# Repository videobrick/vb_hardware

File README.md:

hardware
========

OSHW Video Interface Hardware

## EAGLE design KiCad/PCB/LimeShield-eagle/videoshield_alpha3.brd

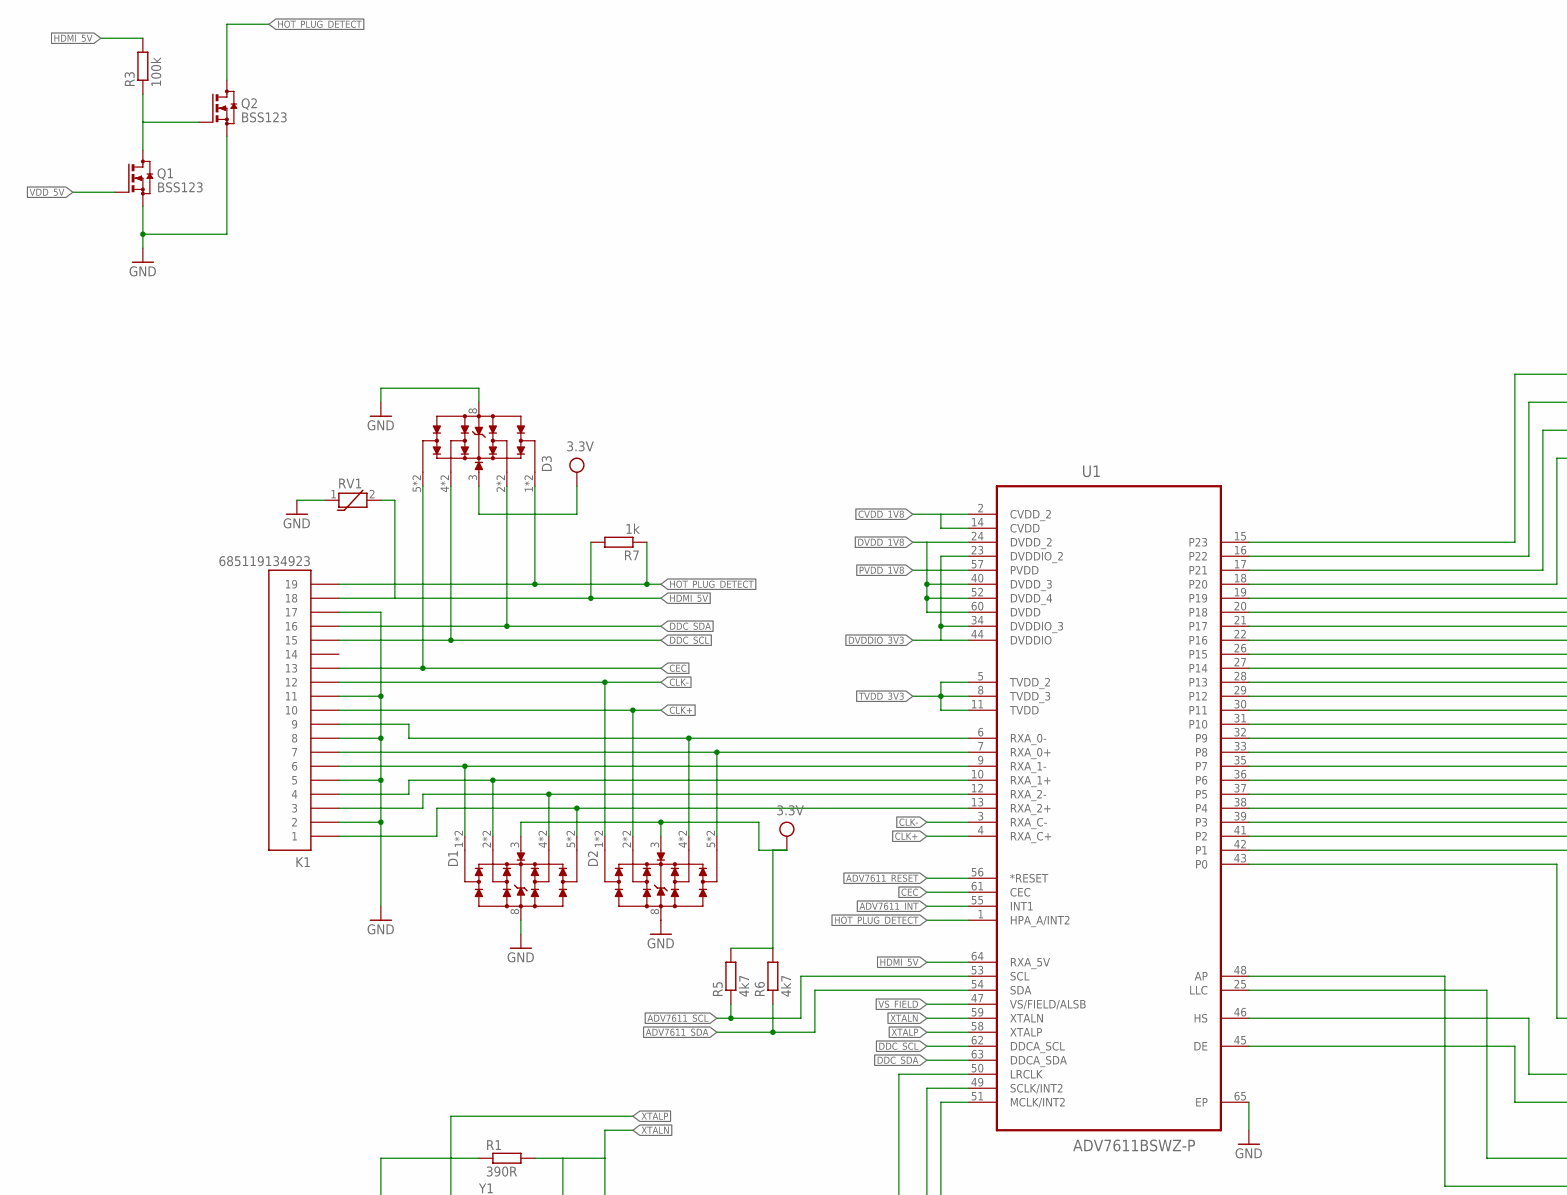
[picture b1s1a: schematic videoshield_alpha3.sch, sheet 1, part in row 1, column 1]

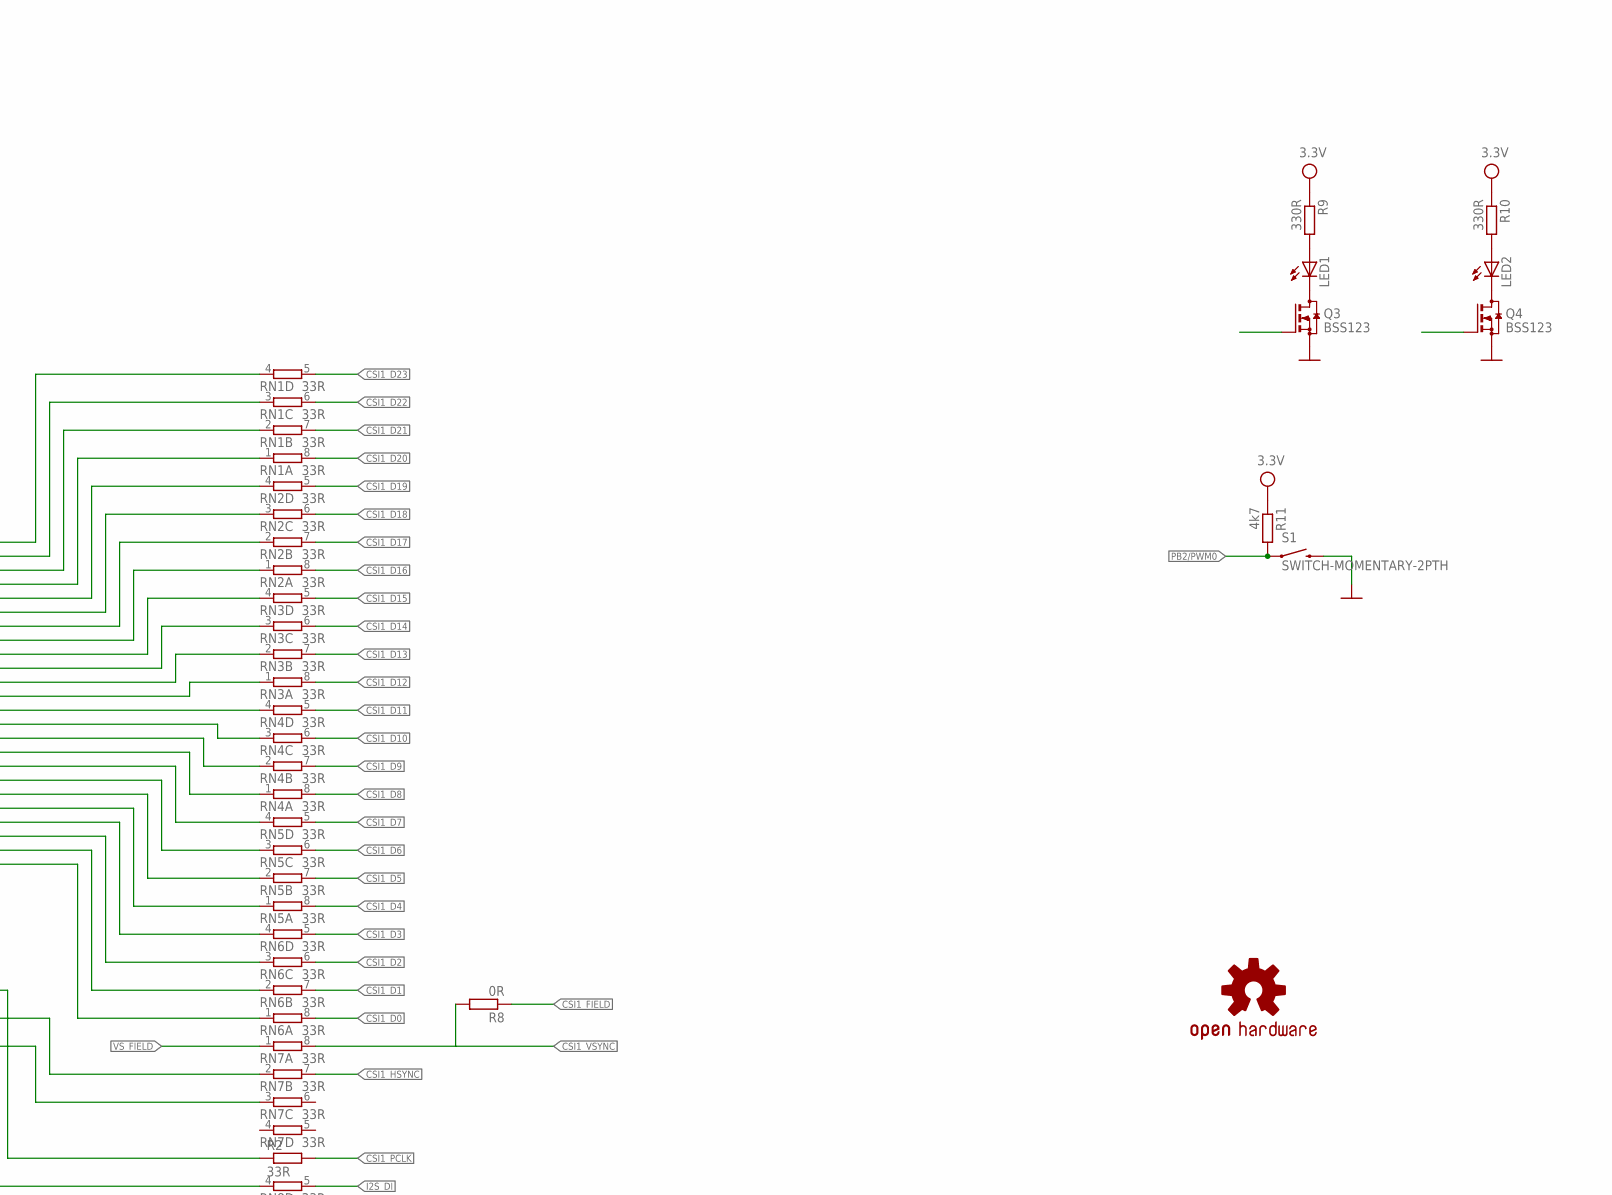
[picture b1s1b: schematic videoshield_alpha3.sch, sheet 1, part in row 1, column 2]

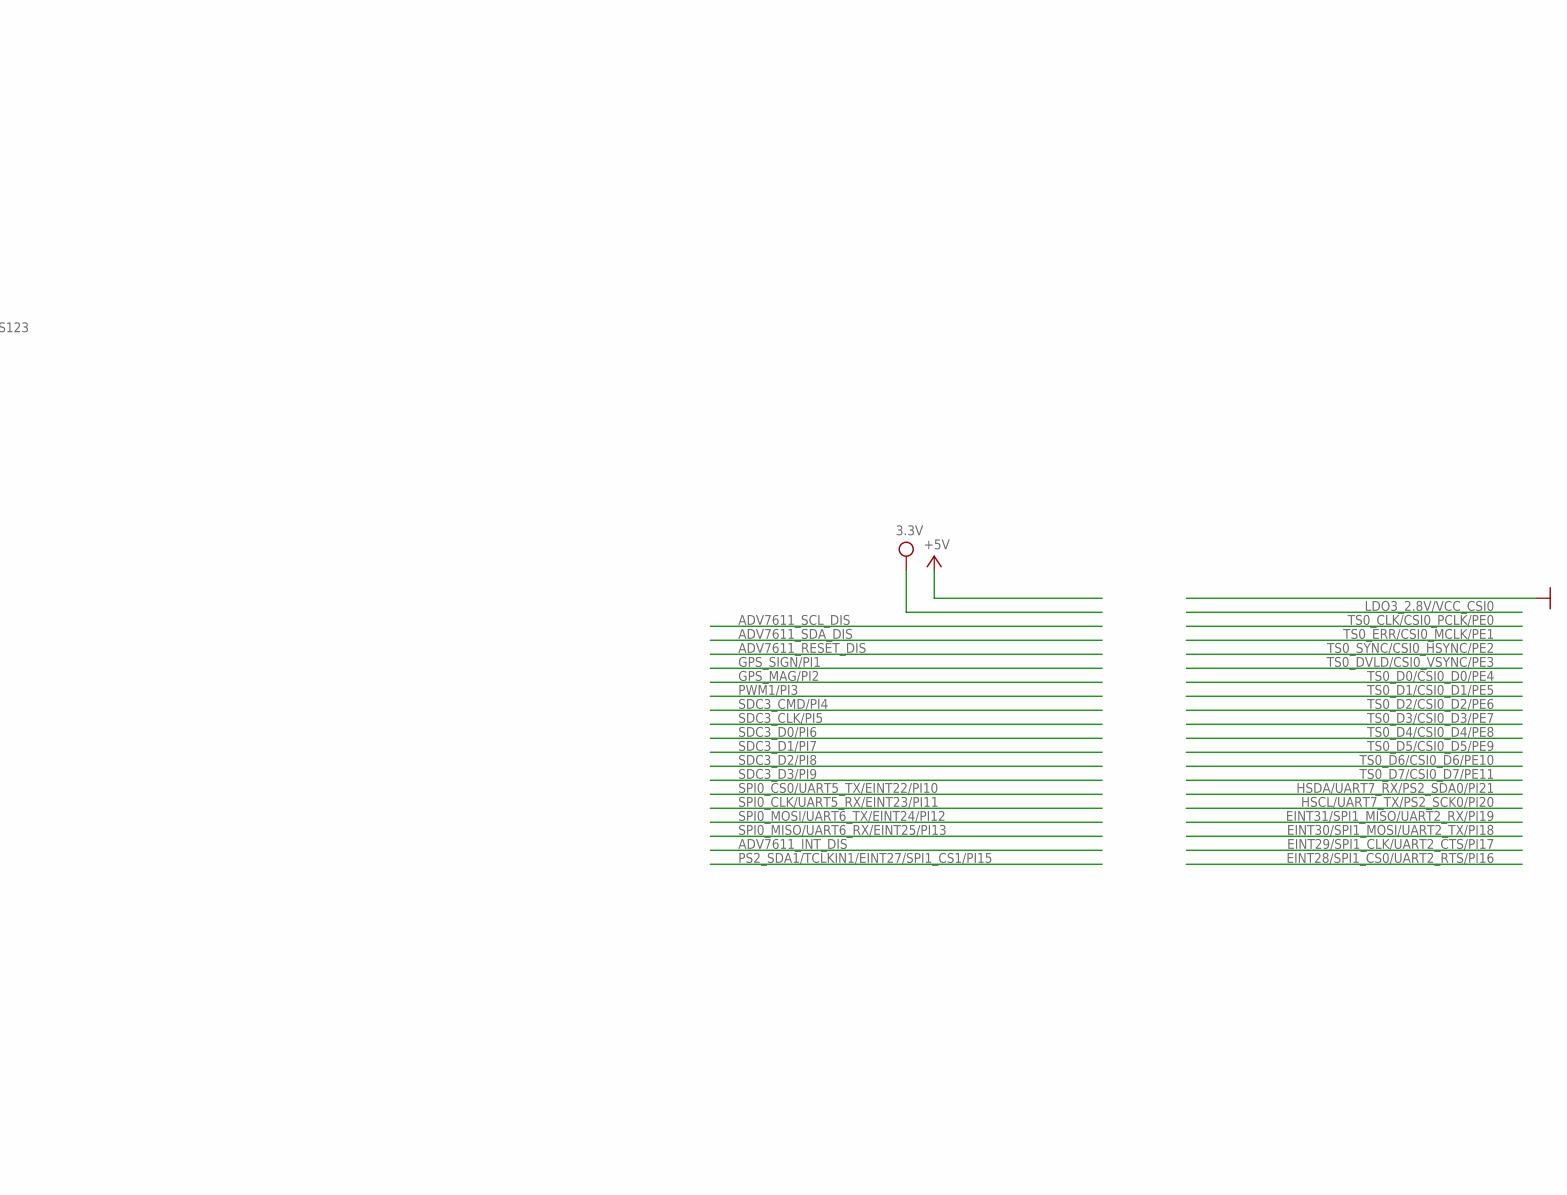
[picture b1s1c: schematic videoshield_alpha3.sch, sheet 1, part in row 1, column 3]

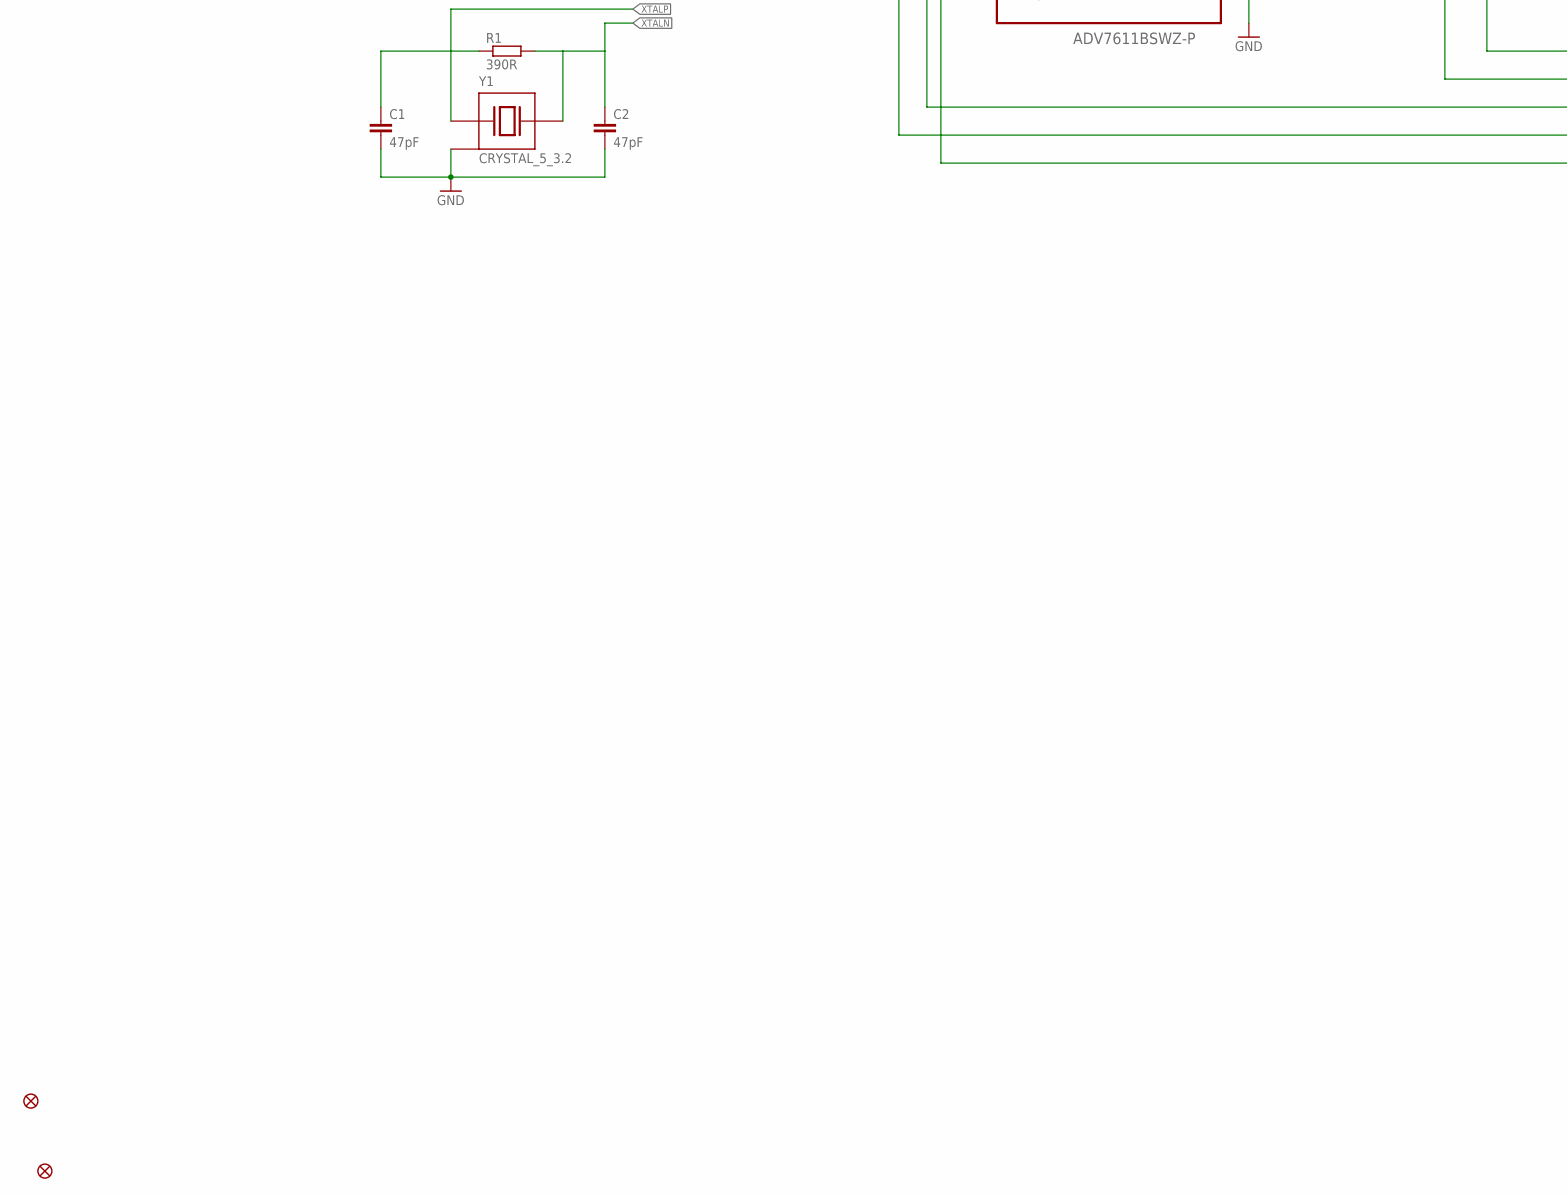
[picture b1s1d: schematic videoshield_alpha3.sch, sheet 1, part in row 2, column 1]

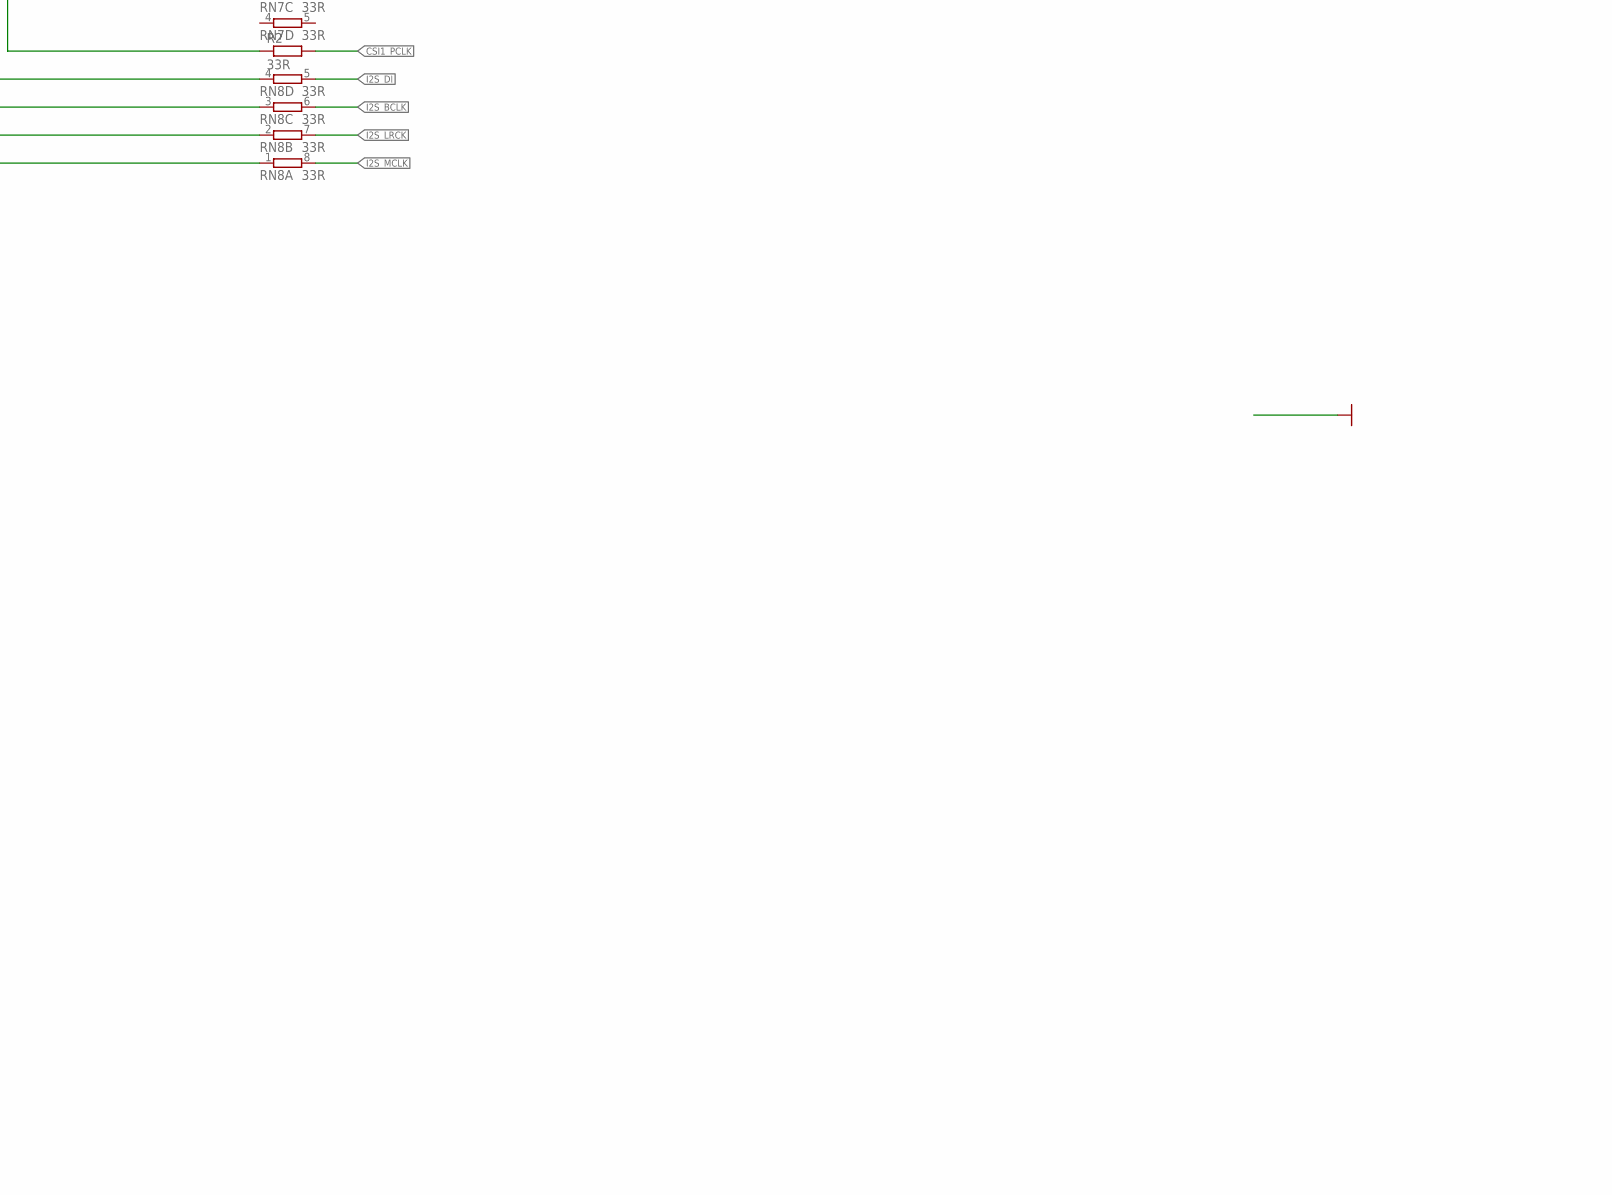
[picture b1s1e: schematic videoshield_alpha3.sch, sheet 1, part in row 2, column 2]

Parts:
C1, C2: 47pF; C0402
D1, D2, D3: WE-TVS_82401444; WE-TVS_MSOP-10L
FID1: FIDUCIALUFIDUCIAL; MICRO-FIDUCIAL
FID2: FIDUCIAL1X2; FIDUCIAL-1X2
K1: 685119134923
LED1, LED2: LEDCHIPLED_0805; CHIPLED_0805
LOGO1: OSHW-LOGOL; OSHW-LOGO-L
Q1, Q2, Q3, Q4: BSS123; SOT23
R1: 390R; R0402
R2: 33R; R0402
R3: 100k; R0402
R5, R6, R11: 4k7; R0402
R7: 1k; R0402
R8: 0R; R0402
R9, R10: 330R; R0402
RN1, RN2, RN3, RN4, RN5, RN6, RN7, RN8: 33R; 4X0402ARV341
RV1: WE-VS-82537040_0402; WESURGE_0402
S1: SWITCH-MOMENTARY-2PTH; TACTILE-PTH
U1: ADV7611BSWZ-P; QFP50P1200X1200X160-65N
Y1: CRYSTAL_5_3.2; 5MM_3.2MM

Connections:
ADV7611_INT: U1.55 (INT1); also elsewhere on the board
ADV7611_RESET: U1.56 (*RESET); also elsewhere on the board
ADV7611_SCL: R5.1, U1.53 (SCL); also elsewhere on the board
ADV7611_SDA: R6.1, U1.54 (SDA); also elsewhere on the board
CEC: D3.5 (4), D3.6 (4), K1.13, U1.61 (CEC)
CLK+: D2.2, D2.9 (2), K1.10, U1.4 (RXA_C+)
CLK-: D2.1, D2.10 (1), K1.12, U1.3 (RXA_C-)
CSI1_D0: RN6.8 (2); also elsewhere on the board
CSI1_D1: RN6.7 (2); also elsewhere on the board
CSI1_D2: RN6.6 (2); also elsewhere on the board
CSI1_D3: RN6.5 (2); also elsewhere on the board
CSI1_D4: RN5.8 (2); also elsewhere on the board
CSI1_D5: RN5.7 (2); also elsewhere on the board
CSI1_D6: RN5.6 (2); also elsewhere on the board
CSI1_D7: RN5.5 (2); also elsewhere on the board
CSI1_D8: RN4.8 (2); also elsewhere on the board
CSI1_D9: RN4.7 (2); also elsewhere on the board
CSI1_D10: RN4.6 (2); also elsewhere on the board
CSI1_D11: RN4.5 (2); also elsewhere on the board
CSI1_D12: RN3.8 (2); also elsewhere on the board
CSI1_D13: RN3.7 (2); also elsewhere on the board
CSI1_D14: RN3.6 (2); also elsewhere on the board
CSI1_D15: RN3.5 (2); also elsewhere on the board
CSI1_D16: RN2.8 (2); also elsewhere on the board
CSI1_D17: RN2.7 (2); also elsewhere on the board
CSI1_D18: RN2.6 (2); also elsewhere on the board
CSI1_D19: RN2.5 (2); also elsewhere on the board
CSI1_D20: RN1.8 (2); also elsewhere on the board
CSI1_D21: RN1.7 (2); also elsewhere on the board
CSI1_D22: RN1.6 (2); also elsewhere on the board
CSI1_D23: RN1.5 (2); also elsewhere on the board
CSI1_FIELD: R8.1; also elsewhere on the board
CSI1_HSYNC: RN7.7 (2); also elsewhere on the board
CSI1_PCLK: R2.2; also elsewhere on the board
CSI1_VSYNC: R8.2, RN7.8 (2); also elsewhere on the board
CVDD_1V8: U1.2 (CVDD_2), U1.14 (CVDD); also elsewhere on the board
DDC_SCL: D3.4 (3), D3.7 (3), K1.15, U1.62 (DDCA_SCL)
DDC_SDA: D3.2, D3.9 (2), K1.16, U1.63 (DDCA_SDA)
DVDDIO_3V3: U1.23 (DVDDIO_2), U1.34 (DVDDIO_3), U1.44 (DVDDIO); also elsewhere on the board
DVDD_1V8: U1.24 (DVDD_2), U1.40 (DVDD_3), U1.52 (DVDD_4), U1.60 (DVDD); also elsewhere on the board
GND: C1.2, C2.2, D1.8 (GND), D2.8 (GND), D3.8 (GND), K1.2, K1.5, K1.8, K1.11, K1.17, Q1.2 (S), Q2.2 (S), Q3.2 (S), Q4.2 (S), RV1.1, S1.3 (2), U1.65 (EP), Y1.P$2 (3), Y1.P$4# (3); also elsewhere on the board
GPIO2: Q4.1 (G); also elsewhere on the board
GPIO3: Q3.1 (G); also elsewhere on the board
HDMI_5V: K1.18, R3.2, R7.2, RV1.2, U1.64 (RXA_5V)
HOT_PLUG_DETECT: D3.1, D3.10 (1), K1.19, Q2.3 (D), R7.1, U1.1 (HPA_A/INT2)
I2S_BCLK: RN8.6 (2); also elsewhere on the board
I2S_DI: RN8.5 (2); also elsewhere on the board
I2S_LRCK: RN8.7 (2); also elsewhere on the board
I2S_MCLK: RN8.8 (2); also elsewhere on the board
unnamed: D1.5 (4), D1.6 (4), K1.1, U1.13 (RXA_2+)
unnamed: D1.4 (3), D1.7 (3), K1.3, U1.12 (RXA_2-)
unnamed: D1.2, D1.9 (2), K1.4, U1.10 (RXA_1+)
unnamed: D1.1, D1.10 (1), K1.6, U1.9 (RXA_1-)
unnamed: D2.5 (4), D2.6 (4), K1.7, U1.7 (RXA_0+)
unnamed: D2.4 (3), D2.7 (3), K1.9, U1.6 (RXA_0-)
unnamed: RN1.4 (1), U1.15 (P23)
unnamed: RN1.3 (1), U1.16 (P22)
unnamed: RN1.2 (1), U1.17 (P21)
unnamed: RN1.1, U1.18 (P20)
unnamed: RN2.4 (1), U1.19
unnamed: RN2.3 (1), U1.20 (P18)
unnamed: RN2.2 (1), U1.21 (P17)
unnamed: RN2.1, U1.22 (P16)
unnamed: RN3.4 (1), U1.26 (P15)
unnamed: RN3.3 (1), U1.27 (P14)
unnamed: RN3.2 (1), U1.28 (P13)
unnamed: RN3.1, U1.29 (P12)
unnamed: RN4.4 (1), U1.30 (P11)
unnamed: RN4.3 (1), U1.31 (P10)
unnamed: RN4.2 (1), U1.32 (P9)
unnamed: RN4.1, U1.33 (P8)
unnamed: RN5.4 (1), U1.35 (P7)
unnamed: RN5.3 (1), U1.36 (P6)
unnamed: RN5.2 (1), U1.37 (P5)
unnamed: RN5.1, U1.38 (P4)
unnamed: RN6.4 (1), U1.39 (P3)
unnamed: RN6.3 (1), U1.41 (P2)
unnamed: RN6.2 (1), U1.42 (P1)
unnamed: RN6.1, U1.43 (P0)
unnamed: RN8.4 (1), U1.48 (AP)
unnamed: RN7.2 (1), U1.46 (HS)
unnamed: RN7.3 (1), U1.45 (DE)
unnamed: R2.1, U1.25 (LLC)
unnamed: RN8.3 (1), U1.49 (SCLK/INT2)
unnamed: Q1.3 (D), Q2.1 (G), R3.1
unnamed: RN8.2 (1), U1.50 (LRCLK)
unnamed: RN8.1, U1.51 (MCLK/INT2)
unnamed: LED1.C, Q3.3 (D)
unnamed: LED1.A, R9.2
unnamed: LED2.A, R10.2
unnamed: LED2.C, Q4.3 (D)
PB2/PWM0: R11.2, S1.1; also elsewhere on the board
PVDD_1V8: U1.57 (PVDD); also elsewhere on the board
TVDD_3V3: U1.5 (TVDD_2), U1.8 (TVDD_3), U1.11 (TVDD); also elsewhere on the board
VCC: D1.3 (VDD), D2.3 (VDD), D3.3 (VDD), R5.2, R6.2, R9.1, R10.1, R11.1; also elsewhere on the board
VDD_5V: Q1.1 (G); also elsewhere on the board
VS_FIELD: RN7.1, U1.47 (VS/FIELD/ALSB)
XTALN: C2.1, R1.2, U1.59 (XTALN), Y1.P$3 (2)
XTALP: C1.1, R1.1, U1.58 (XTALP), Y1.P$1 (1)

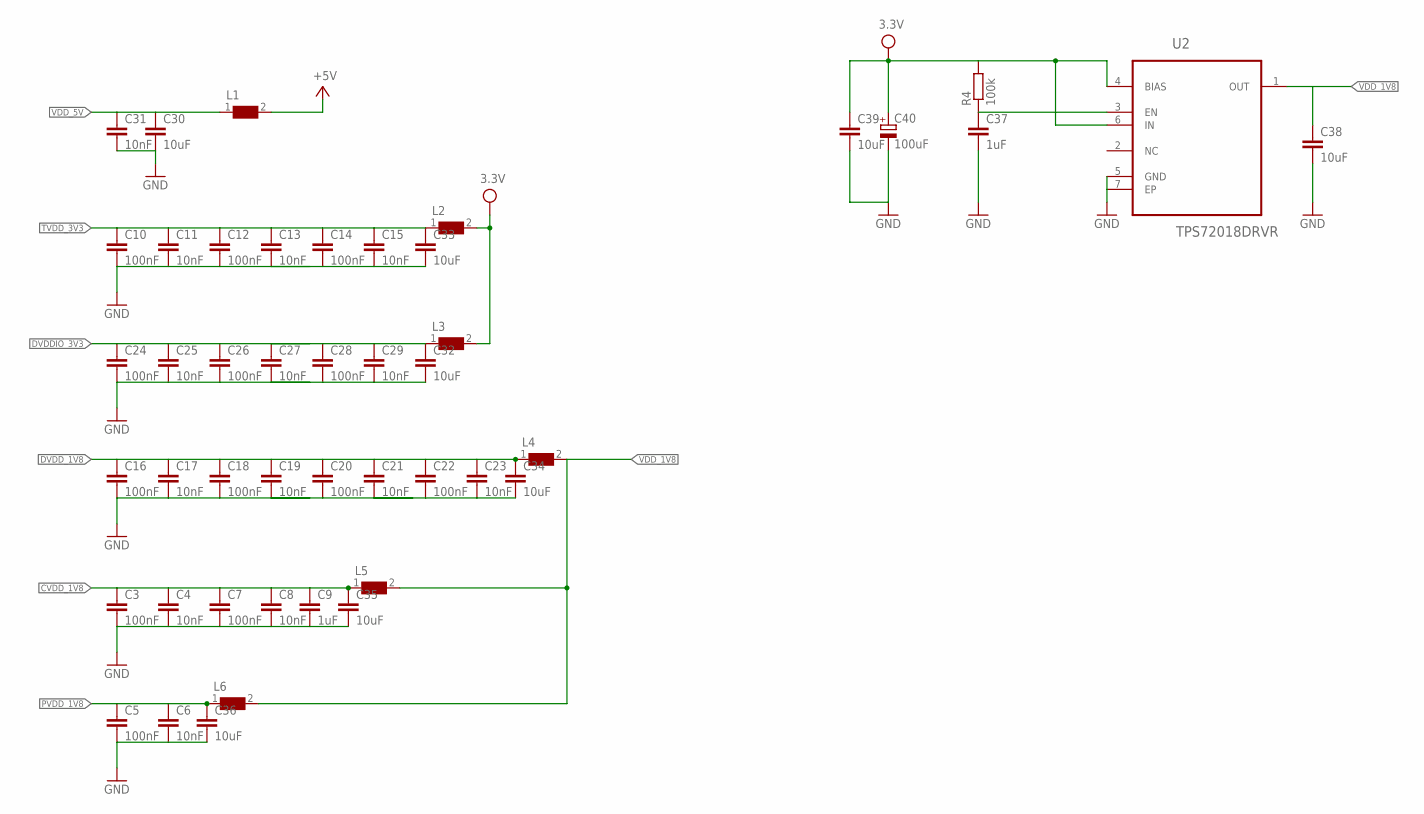
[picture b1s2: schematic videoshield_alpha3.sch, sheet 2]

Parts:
C3, C5, C7, C10, C12, C14, C16, C18, C20, C22, C24, C26, C28: 100nF; C0402
C4, C6, C8, C11, C13, C15, C17, C19, C21, C23, C25, C27, C29, C31: 10nF; C0402
C9, C37: 1uF; C0603
C30, C32, C33, C34, C35, C36, C38, C39: 10uF; C0805
C40: 100uF; 153CLV-0405
L1, L2, L3, L4, L5, L6: WE-CBF-742792040_0805; 0805
R4: 100k; R0402
U2: TPS72018DRVR; SON65P200X200X80-7N

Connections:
+5V: L1.2; also elsewhere on the board
CVDD_1V8: C3.1, C4.1, C7.1, C8.1, C9.1, C35.1, L5.1; also elsewhere on the board
DVDDIO_3V3: C24.1, C25.1, C26.1, C27.1, C28.1, C29.1, C32.1, L3.1; also elsewhere on the board
DVDD_1V8: C16.1, C17.1, C18.1, C19.1, C20.1, C21.1, C22.1, C23.1, C34.1, L4.1; also elsewhere on the board
GND: C3.2, C4.2, C5.2, C6.2, C7.2, C8.2, C9.2, C10.2, C11.2, C12.2, C13.2, C14.2, C15.2, C16.2, C17.2, C18.2, C19.2, C20.2, C21.2, C22.2, C23.2, C24.2, C25.2, C26.2, C27.2, C28.2, C29.2, C30.2, C31.2, C32.2, C33.2, C34.2, C35.2, C36.2, C37.2, C38.2, C39.2, C40.-, U2.5 (GND), U2.7 (EP); also elsewhere on the board
unnamed: C37.1, R4.1, U2.3 (EN)
PVDD_1V8: C5.1, C6.1, C36.1, L6.1; also elsewhere on the board
TVDD_3V3: C10.1, C11.1, C12.1, C13.1, C14.1, C15.1, C33.1, L2.1; also elsewhere on the board
VCC: C39.1, C40.+, L2.2, L3.2, R4.2, U2.4 (BIAS), U2.6 (IN); also elsewhere on the board
VDD_1V8: C38.1, L4.2, L5.2, L6.2, U2.1 (OUT)
VDD_5V: C30.1, C31.1, L1.1; also elsewhere on the board

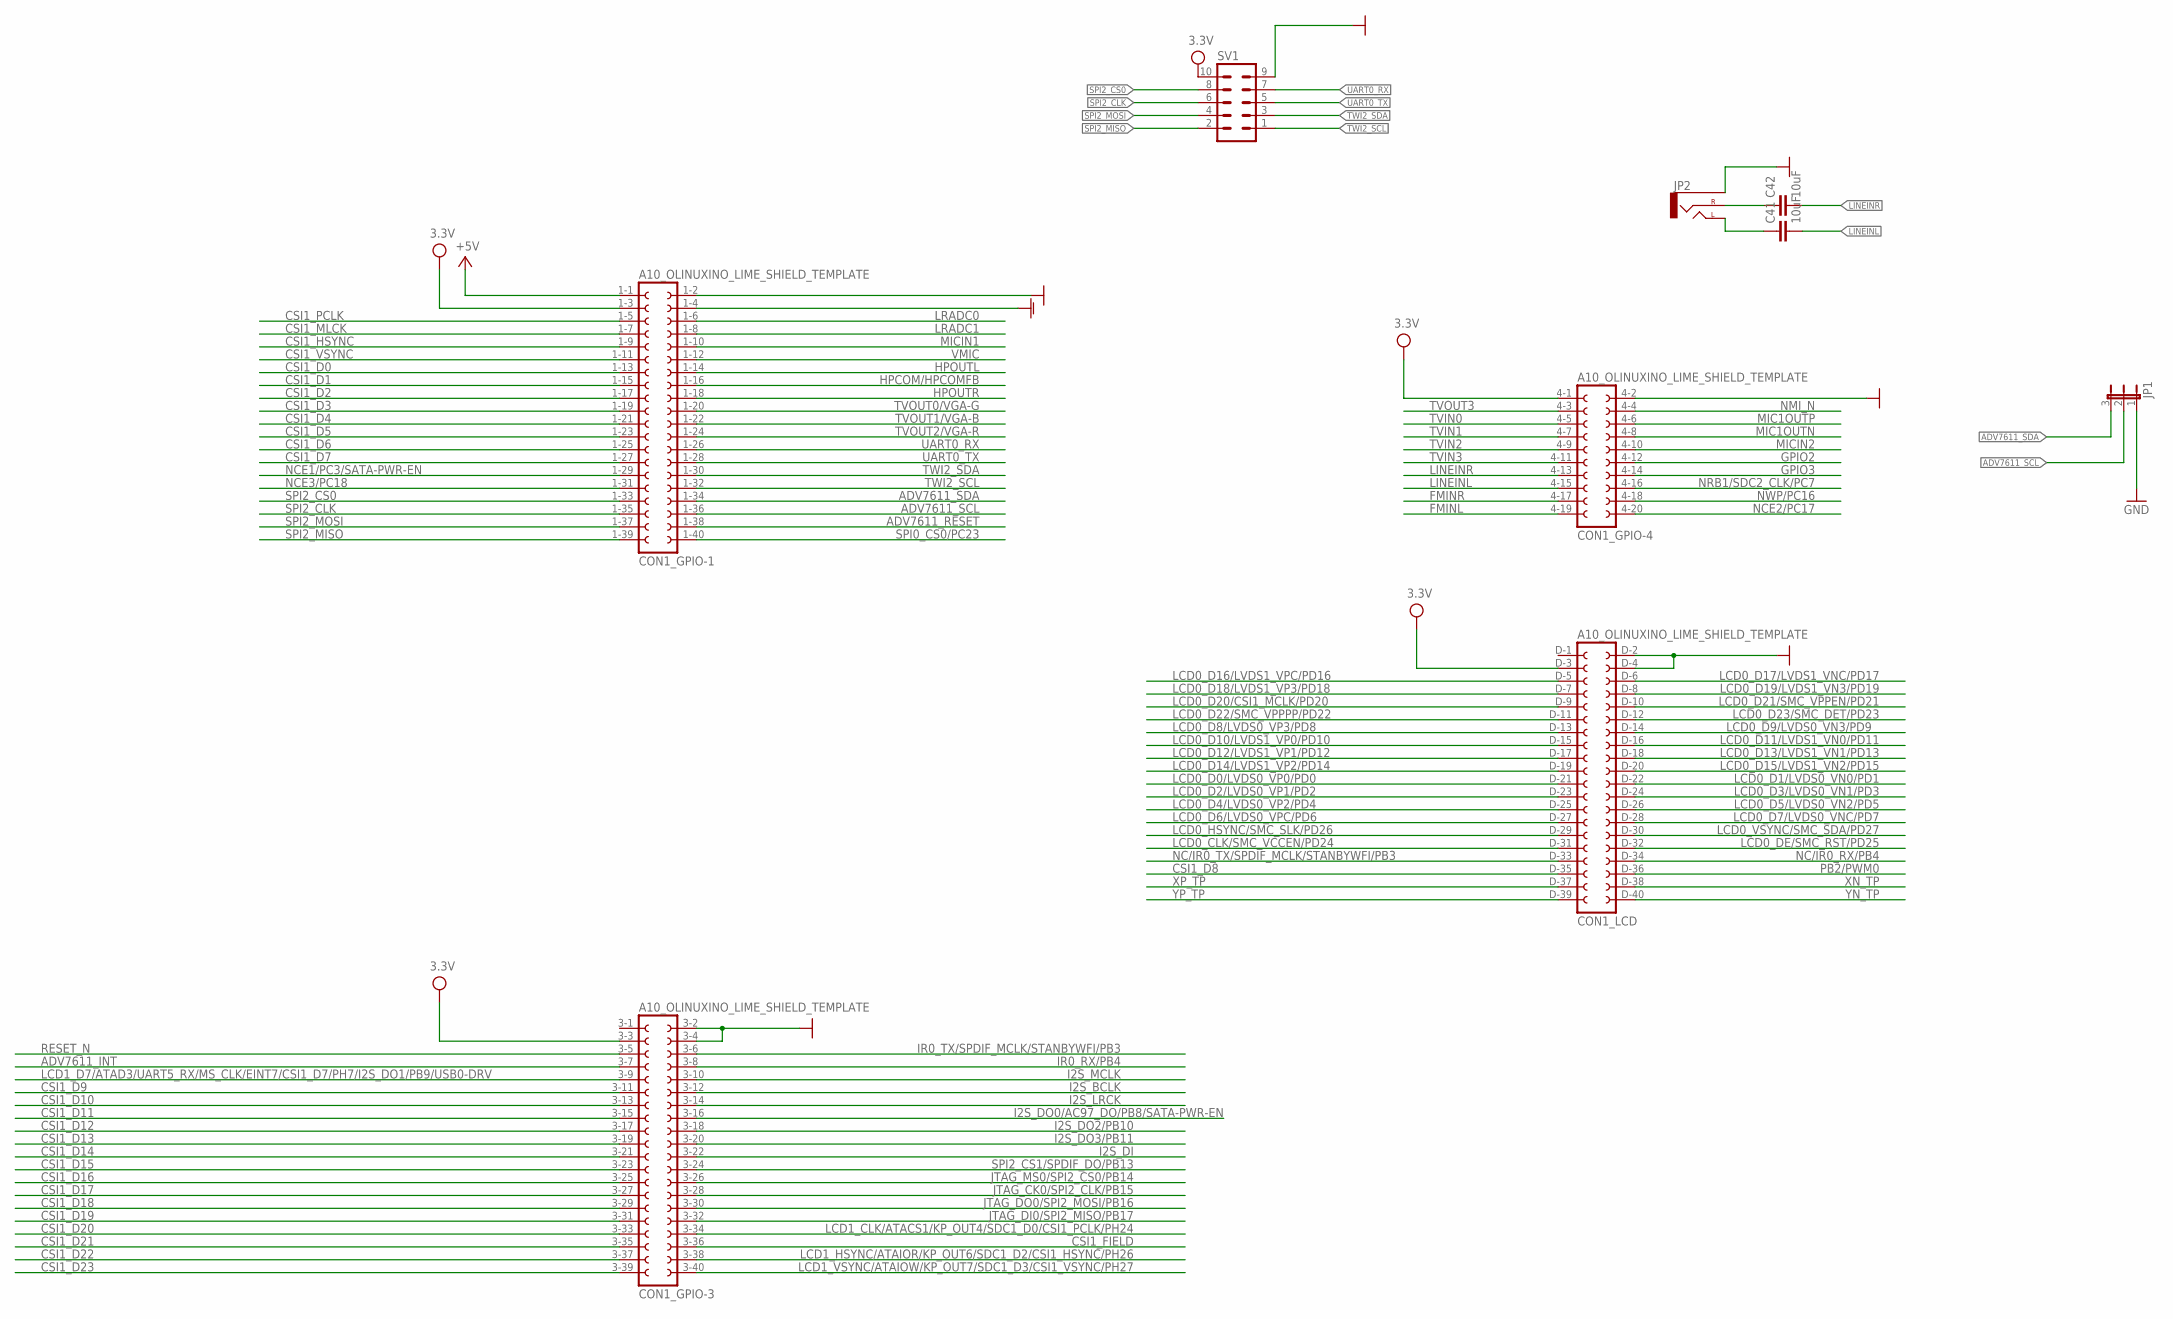
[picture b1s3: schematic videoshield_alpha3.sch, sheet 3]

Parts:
C41, C42: 10uF; C0805
CON1: A10_OLINUXINO_LIME_SHIELD_TEMPLATE; A10_OLINUXINO_LIME_SHIELD
JP1: JP2E; JP2
JP2: AUDIO-JACKPTH; AUDIO-JACK
SV1: MA05-2

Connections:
+5V: CON1.1-1 (1); also elsewhere on the board
ADV7611_INT: CON1.3-7 (7); also elsewhere on the board
ADV7611_RESET: CON1.1-38 (38); also elsewhere on the board
ADV7611_SCL: CON1.1-36 (36), JP1.2; also elsewhere on the board
ADV7611_SDA: CON1.1-34 (34), JP1.3; also elsewhere on the board
CSI1_D0: CON1.1-13 (13); also elsewhere on the board
CSI1_D1: CON1.1-15 (15); also elsewhere on the board
CSI1_D2: CON1.1-17 (17); also elsewhere on the board
CSI1_D3: CON1.1-19 (19); also elsewhere on the board
CSI1_D4: CON1.1-21 (21); also elsewhere on the board
CSI1_D5: CON1.1-23 (23); also elsewhere on the board
CSI1_D6: CON1.1-25 (25); also elsewhere on the board
CSI1_D7: CON1.1-27 (27); also elsewhere on the board
CSI1_D8: CON1.D-35 (35); also elsewhere on the board
CSI1_D9: CON1.3-11 (11); also elsewhere on the board
CSI1_D10: CON1.3-13 (13); also elsewhere on the board
CSI1_D11: CON1.3-15 (15); also elsewhere on the board
CSI1_D12: CON1.3-17 (17); also elsewhere on the board
CSI1_D13: CON1.3-19 (19); also elsewhere on the board
CSI1_D14: CON1.3-21 (21); also elsewhere on the board
CSI1_D15: CON1.3-23 (23); also elsewhere on the board
CSI1_D16: CON1.3-25 (25); also elsewhere on the board
CSI1_D17: CON1.3-27 (27); also elsewhere on the board
CSI1_D18: CON1.3-29 (29); also elsewhere on the board
CSI1_D19: CON1.3-31 (31); also elsewhere on the board
CSI1_D20: CON1.3-33 (33); also elsewhere on the board
CSI1_D21: CON1.3-35 (35); also elsewhere on the board
CSI1_D22: CON1.3-37 (37); also elsewhere on the board
CSI1_D23: CON1.3-39 (39); also elsewhere on the board
CSI1_FIELD: CON1.3-36 (36); also elsewhere on the board
CSI1_HSYNC: CON1.1-9 (9); also elsewhere on the board
CSI1_MLCK: CON1.1-7 (7)
CSI1_PCLK: CON1.1-5 (5); also elsewhere on the board
CSI1_VSYNC: CON1.1-11 (11); also elsewhere on the board
FMINL: CON1.4-19 (19)
FMINR: CON1.4-17 (17)
GND: CON1.1-2 (2), CON1.3-2 (2), CON1.3-4 (4), CON1.4-2 (2), CON1.D-2 (2), CON1.D-4 (4), JP2.SLEEVE, SV1.9; also elsewhere on the board
GNDA: CON1.1-4 (4)
GPIO2: CON1.4-12 (12); also elsewhere on the board
GPIO3: CON1.4-14 (14); also elsewhere on the board
HPCOM/HPCOMFB: CON1.1-16 (16)
HPOUTL: CON1.1-14 (14)
HPOUTR: CON1.1-18 (18)
I2S_BCLK: CON1.3-12 (12); also elsewhere on the board
I2S_DI: CON1.3-22 (22); also elsewhere on the board
I2S_DO0/AC97_DO/PB8/SATA-PWR-EN: CON1.3-16 (16)
I2S_DO2/PB10: CON1.3-18 (18)
I2S_DO3/PB11: CON1.3-20 (20)
I2S_LRCK: CON1.3-14 (14); also elsewhere on the board
I2S_MCLK: CON1.3-10 (10); also elsewhere on the board
IR0_RX/PB4: CON1.3-8 (8)
IR0_TX/SPDIF_MCLK/STANBYWFI/PB3: CON1.3-6 (6)
JTAG_CK0/SPI2_CLK/PB15: CON1.3-28 (28)
JTAG_DI0/SPI2_MISO/PB17: CON1.3-32 (32)
JTAG_DO0/SPI2_MOSI/PB16: CON1.3-30 (30)
JTAG_MS0/SPI2_CS0/PB14: CON1.3-26 (26)
LCD0_CLK/SMC_VCCEN/PD24: CON1.D-31 (31)
LCD0_D0/LVDS0_VP0/PD0: CON1.D-21 (21)
LCD0_D1/LVDS0_VN0/PD1: CON1.D-22 (22)
LCD0_D2/LVDS0_VP1/PD2: CON1.D-23 (23)
LCD0_D3/LVDS0_VN1/PD3: CON1.D-24 (24)
LCD0_D5/LVDS0_VN2/PD5: CON1.D-26 (26)
LCD0_D6/LVDS0_VPC/PD6: CON1.D-27 (27)
LCD0_D9/LVDS0_VN3/PD9: CON1.D-14 (14)
LCD0_D10/LVDS1_VP0/PD10: CON1.D-15 (15)
LCD0_D11/LVDS1_VN0/PD11: CON1.D-16 (16)
LCD0_D12/LVDS1_VP1/PD12: CON1.D-17 (17)
LCD0_D13/LVDS1_VN1/PD13: CON1.D-18 (18)
LCD0_D14/LVDS1_VP2/PD14: CON1.D-19 (19)
LCD0_D15/LVDS1_VN2/PD15: CON1.D-20 (20)
LCD0_D16/LVDS1_VPC/PD16: CON1.D-5 (5)
LCD0_D17/LVDS1_VNC/PD17: CON1.D-6 (6)
LCD0_D18/LVDS1_VP3/PD18: CON1.D-7 (7)
LCD0_D19/LVDS1_VN3/PD19: CON1.D-8 (8)
LCD0_D20/CSI1_MCLK/PD20: CON1.D-9 (9)
LCD0_D21/SMC_VPPEN/PD21: CON1.D-10 (10)
LCD0_D22/SMC_VPPPP/PD22: CON1.D-11 (11)
LCD0_D23/SMC_DET/PD23: CON1.D-12 (12)
LCD0_DE/SMC_RST/PD25: CON1.D-32 (32)
LCD0_HSYNC/SMC_SLK/PD26: CON1.D-29 (29)
LCD0_VSYNC/SMC_SDA/PD27: CON1.D-30 (30)
LCD1_CLK/ATACS1/KP_OUT4/SDC1_D0/CSI1_PCLK/PH24: CON1.3-34 (34)
LCD1_D7/ATAD3/UART5_RX/MS_CLK/EINT7/CSI1_D7/PH7/I2S_DO1/PB9/USB0-DRV: CON1.3-9 (9)
LCD1_HSYNC/ATAIOR/KP_OUT6/SDC1_D2/CSI1_HSYNC/PH26: CON1.3-38 (38)
LCD1_VSYNC/ATAIOW/KP_OUT7/SDC1_D3/CSI1_VSYNC/PH27: CON1.3-40 (40)
LINEINL: C41.2, CON1.4-15 (15)
LINEINR: C42.2, CON1.4-13 (13)
LRADC0: CON1.1-6 (6)
LRADC1: CON1.1-8 (8)
MIC1OUTN: CON1.4-8 (8)
MIC1OUTP: CON1.4-6 (6)
MICIN1: CON1.1-10 (10)
MICIN2: CON1.4-10 (10)
unnamed: C42.1, JP2.RING (RIGHT)
unnamed: C41.1, JP2.TIP (LEFT)
NC/IR0_RX/PB4: CON1.D-34 (34)
NC/IR0_TX/SPDIF_MCLK/STANBYWFI/PB3: CON1.D-33 (33)
NCE1/PC3/SATA-PWR-EN: CON1.1-29 (29)
NCE2/PC17: CON1.4-20 (20)
NCE3/PC18: CON1.1-31 (31)
NMI_N: CON1.4-4 (4)
NRB1/SDC2_CLK/PC7: CON1.4-16 (16)
NWP/PC16: CON1.4-18 (18)
PB2/PWM0: CON1.D-36 (36); also elsewhere on the board
RESET_N: CON1.3-5 (5)
SPI0_CS0/PC23: CON1.1-40 (40)
SPI2_CLK: CON1.1-35 (35), SV1.6
SPI2_CS0: CON1.1-33 (33), SV1.8
SPI2_CS1/SPDIF_DO/PB13: CON1.3-24 (24)
SPI2_MISO: CON1.1-39 (39), SV1.2
SPI2_MOSI: CON1.1-37 (37), SV1.4
TVIN0: CON1.4-5 (5)
TVIN1: CON1.4-7 (7)
TVIN2: CON1.4-9 (9)
TVIN3: CON1.4-11 (11)
TVOUT0/VGA-G: CON1.1-20 (20)
TVOUT1/VGA-B: CON1.1-22 (22)
TVOUT2/VGA-R: CON1.1-24 (24)
TVOUT3: CON1.4-3 (3)
TWI2_SCL: CON1.1-32 (32), SV1.1
TWI2_SDA: CON1.1-30 (30), SV1.3
UART0_RX: CON1.1-26 (26), SV1.7
UART0_TX: CON1.1-28 (28), SV1.5
VCC: CON1.1-3 (3), CON1.3-3 (3), CON1.4-1 (1), CON1.D-3 (3), SV1.10; also elsewhere on the board
VMIC: CON1.1-12 (12)
XN_TP: CON1.D-38 (38)
XP_TP: CON1.D-37 (37)
YP_TP: CON1.D-39 (39)

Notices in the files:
KiCad/PCB/LimeShield-eagle/videoshield_alpha3.brd:
CC-BY-SA 3.0
parts and their libraries:
InputOutputIO: Copyright: Würth Elektronik
SparkFun-Connectors: Licensing: Creative Commons ShareAlike 4.0 International - https://creativecommons.org/licenses/by-sa/4.0
